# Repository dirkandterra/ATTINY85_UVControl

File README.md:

# ATTINY85_UVControl
Controlling UV LED Strip with ATTINY85 and scrap printer part

The attached code is to run on an ATTINY85, but there is a compiler directive that will allow a build to nano for testing (to have serial)

The ATTINY is programmed using Arduino as ISP.  Hook the wires up accordingly:

Arduino====>Attiny====>Attiny85   
D10=======>RESET======>PIN1   
D11=======>MOS======>PIN5   
D12=======>MISO======>PIN6    
D13=======>SCK======>PIN7   
5V========>VCC======>PIN8 (I just power on the board instead of hooking this up)    
GND======>GND=====>PIN4   
(MOSI,MISO,RESET. 5V for programming is supplied from the device, not the programmer.)

**IMPORTANT**
You will also need a fairly large cap (100-1000uF) across the RST of the Arduino pin (+ side if cap is polarized) and GND.  This is to keep the Nano from resetting itself when programming.  You will also have to upload the Arduino as ISP image to the nano first for it to function properly.

Add "https://raw.githubusercontent.com/damellis/attiny/ide-1.6.x-boards-manager/package_damellis_attiny_index.json" to board manager URLs

Board Settings:
Device: ATTINY25/45/85
Internal Clk: 1MHZ
Processor: ATTINY85
Programmer: Arduino as ISP

Program Description:    
The top button starts the UV timer and the side button toggles between the "set time" mode and the "UV light" mode.   
In the "set time mode", each top button press adds 30 sec to the time.  The top button led flashes once for every minute    
and a quick blip if a 30 sec addition is made.  Default is seven minutes.

For LEDs: (AMARS Black LED Lights Strip for Decoration, DC12V 24W 5050 SMD 2M/6.6FT 390nm-405nm), 54 LEDs were used and draw 500mA

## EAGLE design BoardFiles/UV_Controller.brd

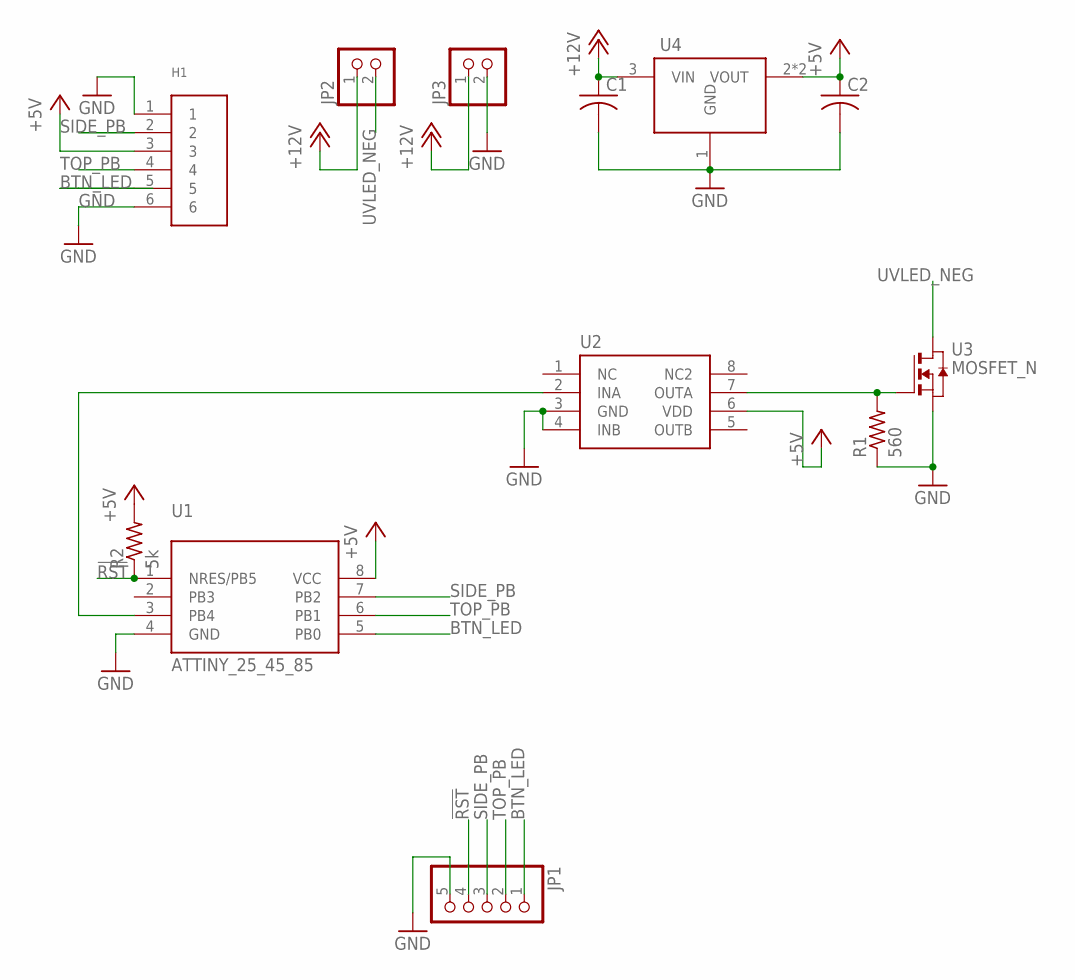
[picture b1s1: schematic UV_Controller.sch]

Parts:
C1, C2: C-USC0805; C0805
H1: 6PIN_RIBBON_CONN_1MM; 6PIN_SMD_CONN_1MM
JP1: PINHD-1X5; 1X05
JP2, JP3: PINHD-1X2; 1X02
R1: 560; R0805
R2: 5k; R0805
U1: ATTINY_25_45_85; SOIC-8
U2: TC427; SOIC-8
U3: MOSFET_N; SOT-23
U4: NCP1117ST50T3G; SOT223

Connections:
!RST: JP1.4, R2.1, U1.1 (NRES/PB5)
+5V: C2.1, H1.3, R2.2, U1.8 (VCC), U2.6 (VDD), U4.2 (VOUT), U4.4 (VOUT)
+12V: C1.1, JP2.1, JP3.1, U4.3 (VIN)
BTN_LED: H1.5, JP1.1, U1.5 (PB0)
GND: C1.2, C2.2, H1.1, H1.6, JP1.5, JP3.2, R1.1, U1.4 (GND), U2.3 (GND), U2.4 (INB), U3.3 (S), U4.1 (GND)
unnamed: U1.3 (PB4), U2.2 (INA)
unnamed: R1.2, U2.7 (OUTA), U3.2 (G)
SIDE_PB: H1.2, JP1.3, U1.7 (PB2)
TOP_PB: H1.4, JP1.2, U1.6 (PB1)
UVLED_NEG: JP2.2, U3.1 (D)

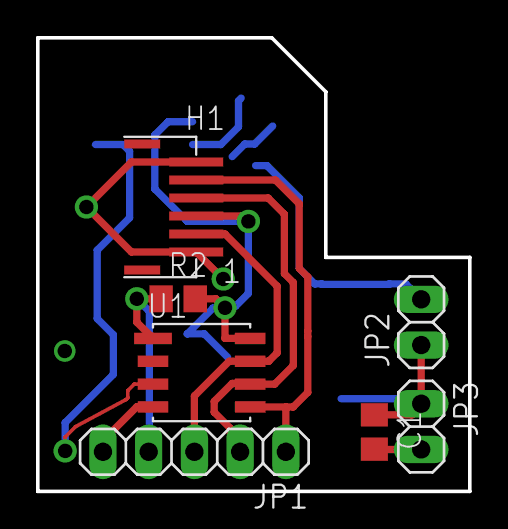
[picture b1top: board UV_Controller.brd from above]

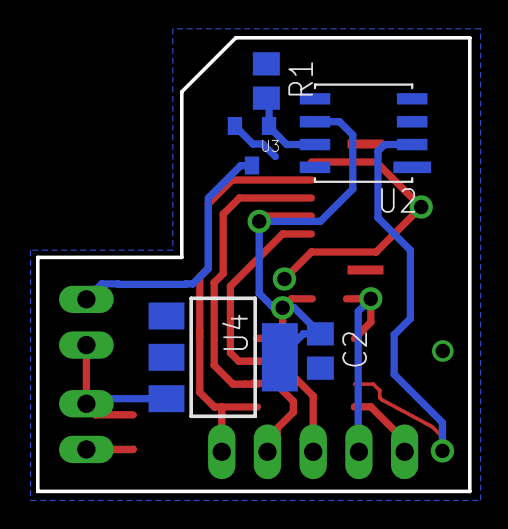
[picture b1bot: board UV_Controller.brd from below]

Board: 2 copper layers, 24.0 x 25.2 mm, 12 parts (5 on the bottom side), 10 nets.

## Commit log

2023-04-27 Update README.md
    initial
2023-04-27 Initial commit
    yes
2023-04-30 Update README.md
    Wiring info
2023-04-30 Add files via upload
    Added Box 3D Files
